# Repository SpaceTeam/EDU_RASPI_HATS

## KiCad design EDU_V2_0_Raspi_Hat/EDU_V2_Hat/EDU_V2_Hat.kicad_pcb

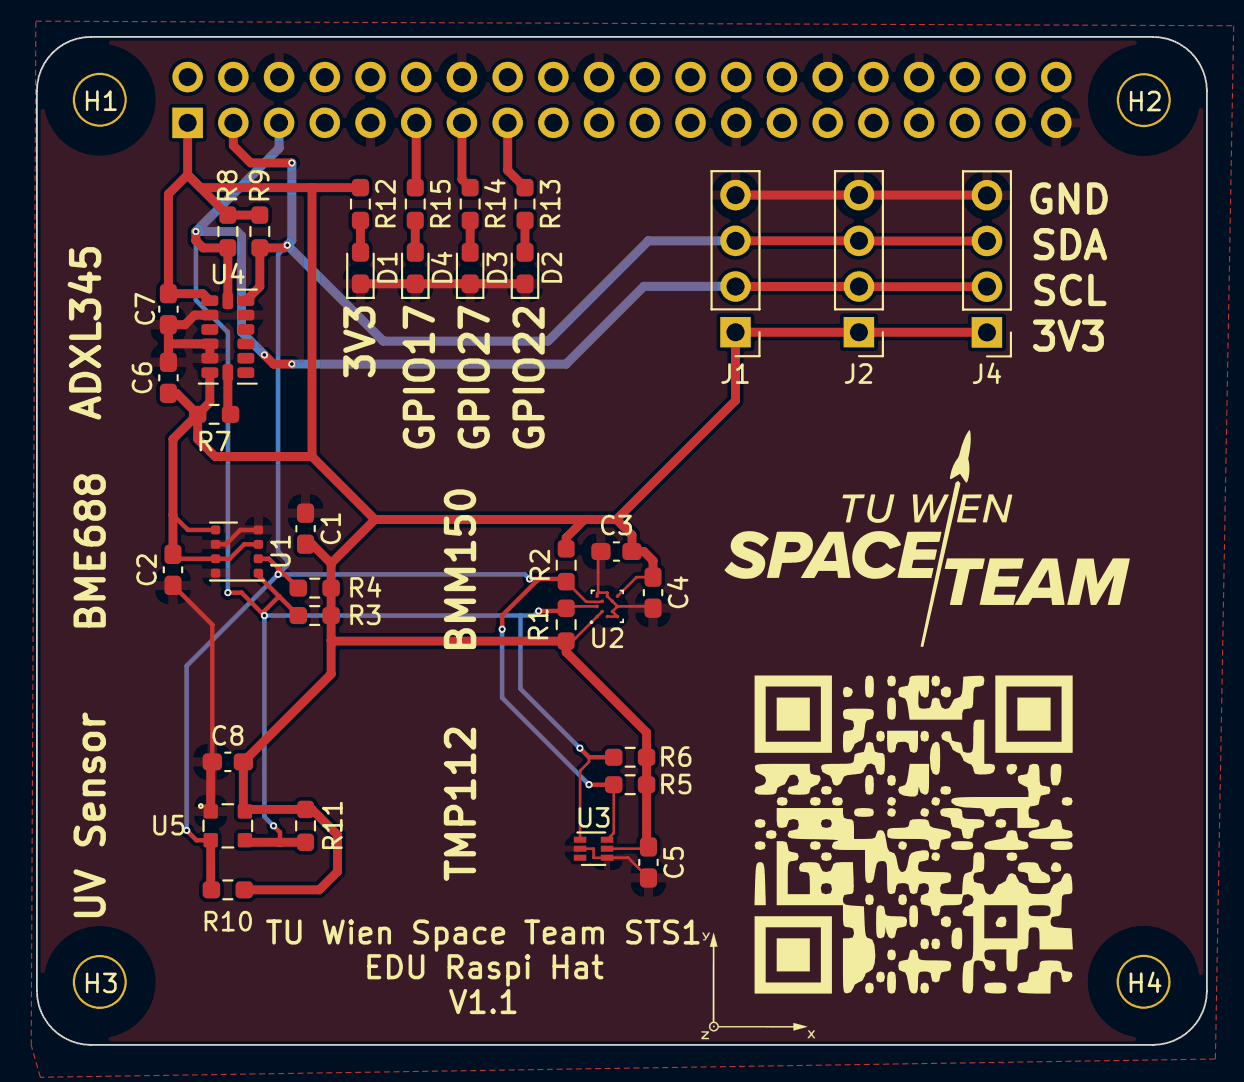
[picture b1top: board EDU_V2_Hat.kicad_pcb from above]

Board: 4 copper layers, 65.0 x 56.0 mm, 41 parts (1 on the bottom side), 12 nets.

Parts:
C1, C2, C3, C4: 100nF; C_0603_1608Metric_Pad1.08x0.95mm_HandSolder
C5: 0.01µF; C_0603_1608Metric_Pad1.08x0.95mm_HandSolder
C6: 0.1µF; C_0603_1608Metric_Pad1.08x0.95mm_HandSolder
C7: 1µF; C_0603_1608Metric_Pad1.08x0.95mm_HandSolder
C8: 1uF; C_0603_1608Metric_Pad1.08x0.95mm_HandSolder
D1, D2, D3, D4: LED; LED_0603_1608Metric_Pad1.05x0.95mm_HandSolder
H1, H2, H3, H4: 3mm_Mounting_Hole; NPTH_3mm_ID
J1, J2, J4: Conn_01x04; PinHeader_1x04_P2.54mm_Vertical
J3: 40HAT; PinSocket_2x20_P2.54mm_Vertical
R1, R2, R10, R11: 4k7; R_0603_1608Metric_Pad0.98x0.95mm_HandSolder
R3, R4, R5, R6, R7, R8, R9: 5k; R_0603_1608Metric_Pad0.98x0.95mm_HandSolder
R12, R13, R14, R15: 1k; R_0603_1608Metric_Pad0.98x0.95mm_HandSolder
U1: BME688; Bosch_LGA-8_3x3mm_P0.8mm_ClockwisePinNumbering
U1#2: coordinate_system; Coordinates
U2: BMM150; WLCSP-12_1.56x1.56mm_P0.4mm
U3: TMP112AIDRLT; SOT-563
U4: ADXL345BCCZ-RL; LGA-14_3x5mm_P0.8mm_LayoutBorder1x6y
U5: GUVA-C32SM; OLGA 2mm x 2,3mm

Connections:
3V3: C1.2, C2.2, C3.2, C4.1, C5.1, C6.1, C7.1, C8.2, J1.1, J2.1, J3.1 (P3V3), J4.1, R1.2, R2.2, R3.2, R4.2, R5.2, R6.2, R7.1, R8.1, R9.1, R10.2, R11.2, R12.1, U1.2 (CSB), U1.6 (VDDIO), U1.8 (VDD), U2.A1 (PS), U2.B2 (VDDIO), U2.E5 (VDD), U3.5 (V+), U4.1 (VDDIO), U4.6 (VS), U5.4 (VCC)
CM_SCL0: J1.2, J2.2, J3.5 (BCM3), J4.2, R1.1, R3.1, R6.1, R8.2, R11.1, U1.4 (SCK), U2.A3 (SCK), U3.1 (SCL), U4.14 (SCL/SCLK), U5.3 (SCL)
CM_SDA0: J1.3, J2.3, J3.3 (BCM2), J4.3, R2.1, R4.1, R5.1, R9.2, R10.1, U1.3 (SDI), U2.B4 (SDI), U3.6 (SDA), U4.13 (SDA/SDI/SDIO), U5.2 (SDA)
GND: C1.1, C2.1, C3.1, C4.2, C5.2, C6.2, C7.2, C8.1, D1.1 (K), D2.1 (K), D3.1 (K), D4.1 (K), J1.4, J2.4, J3.6 (GND), J3.9 (GND), J3.14 (GND), J3.20 (GND), J3.25 (GND), J3.30 (GND), J3.34 (GND), J3.39 (GND), J4.4, U1.1 (GND), U1.5 (SDO), U1.7 (GND), U2.A5 (CSB), U2.C1 (SDO), U2.C5 (GND), U2.D2 (INT), U2.D4 (DRDY), U2.E1 (GND), U2.E3 (GND), U3.2 (GND), U3.4 (ADD0), U4.2 (GND@1), U4.4 (GND@2), U4.5 (GND@3), U4.12 (SDO/ALT/ADDRESS), U5.1 (GND)
GPIO17: J3.11 (BCM17), R15.1
GPIO22: J3.15 (BCM22), R13.1
GPIO27: J3.13 (BCM27), R14.1
unnamed: D1.2 (A), R12.2
unnamed: D2.2 (A), R13.2
unnamed: D3.2 (A), R14.2
unnamed: D4.2 (A), R15.2
unnamed: R7.2, U4.7 (~CS)

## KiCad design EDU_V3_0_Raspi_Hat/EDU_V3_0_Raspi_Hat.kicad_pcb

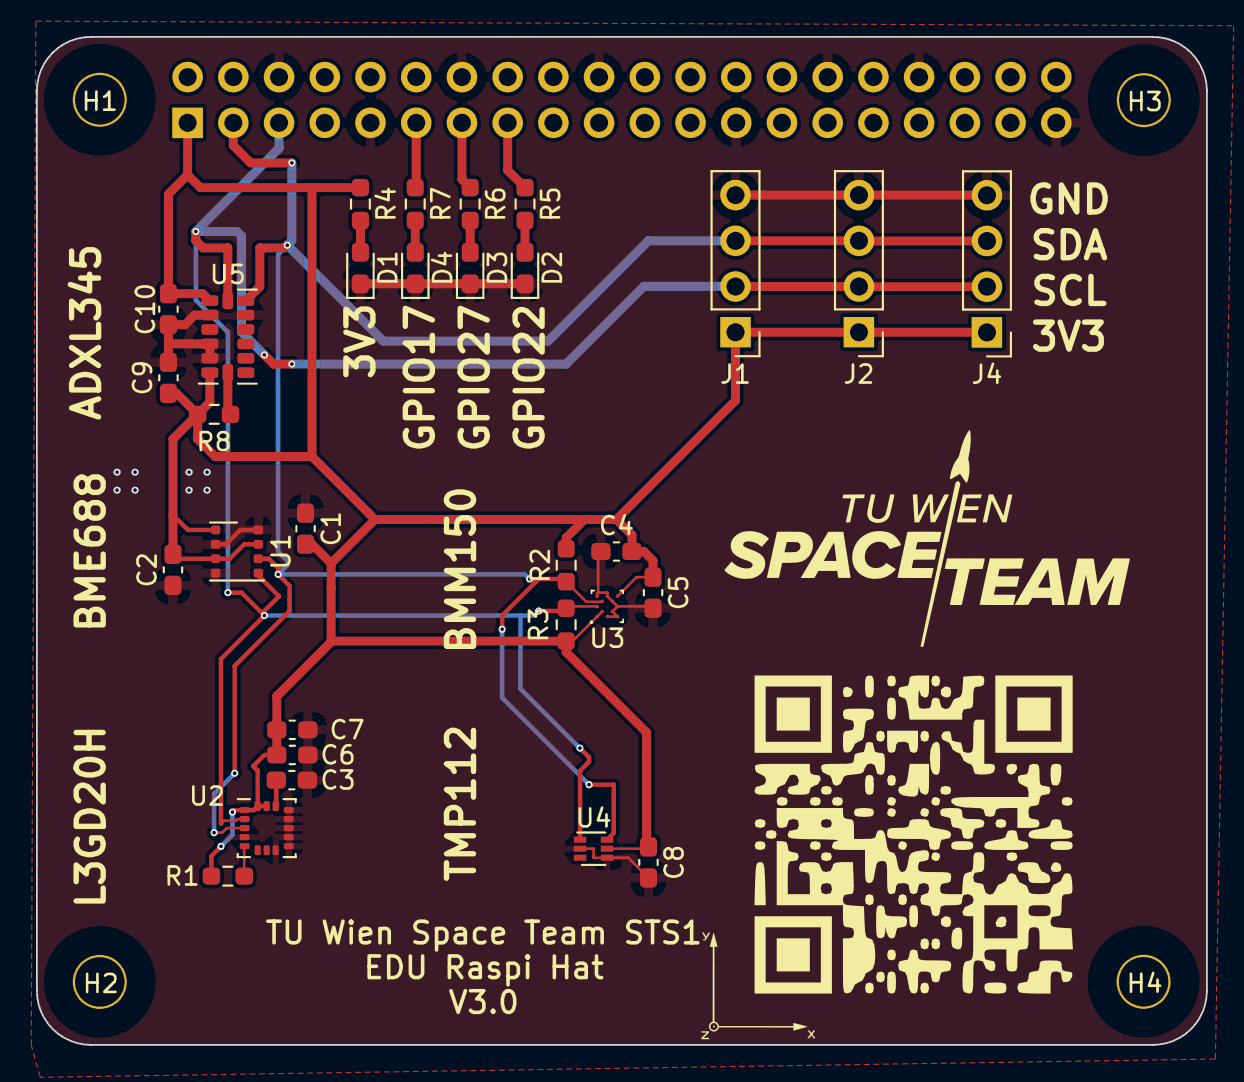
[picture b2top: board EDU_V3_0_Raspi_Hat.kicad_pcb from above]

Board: 4 copper layers, 65.0 x 56.0 mm, 36 parts (1 on the bottom side), 14 nets.

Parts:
C1, C2, C4, C5, C6, C9: 100nF; C_0603_1608Metric_Pad1.08x0.95mm_HandSolder
C3: 10nF 25V; C_0603_1608Metric_Pad1.08x0.95mm_HandSolder
C7: 10uF; C_0603_1608Metric_Pad1.08x0.95mm_HandSolder
C8: 10nF; C_0603_1608Metric_Pad1.08x0.95mm_HandSolder
C10: 1µF; C_0603_1608Metric_Pad1.08x0.95mm_HandSolder
D1, D2, D3, D4: LED; LED_0603_1608Metric_Pad1.05x0.95mm_HandSolder
H1, H2, H3, H4: 3mm_Mounting_Hole; NPTH_3mm_ID
J1, J2, J4: Conn_01x04; PinHeader_1x04_P2.54mm_Vertical
J3: 40HAT; PinSocket_2x20_P2.54mm_Vertical
R1, R2, R3, R8: 4k7; R_0603_1608Metric_Pad0.98x0.95mm_HandSolder
R4, R5, R6, R7: 1k; R_0603_1608Metric_Pad0.98x0.95mm_HandSolder
U1: BME688; Bosch_LGA-8_3x3mm_P0.8mm_ClockwisePinNumbering
U1#2: coordinate_system; Coordinates
U2: L3GD20H; LGA-16_3x3mm_P0.5mm_LayoutBorder3x5y
U3: BMM150; WLCSP-12_1.56x1.56mm_P0.4mm
U4: TMP112AIDRLT; SOT-563
U5: ADXL345BCCZ-RL; LGA-14_3x5mm_P0.8mm_LayoutBorder1x6y

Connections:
3V3: C1.2, C2.2, C4.2, C5.1, C6.1, C7.1, C8.1, C9.1, C10.1, J1.1, J2.1, J3.1 (P3V3), J4.1, R1.1, R2.2, R3.2, R4.1, R8.1, U1.2 (CSB), U1.6 (VDDIO), U1.8 (VDD), U2.1 (VDD_IO), U2.15 (RES@4), U2.16 (VDD), U3.A1 (PS), U3.B2 (VDDIO), U3.E5 (VDD), U4.5 (V+), U5.1 (VDDIO), U5.6 (VS)
CM_SCL0: J1.2, J2.2, J3.5 (BCM3), J4.2, R3.1, U1.4 (SCK), U2.2 (SCL/SPC), U3.A3 (SCK), U4.1 (SCL), U5.14 (SCL/SCLK)
CM_SDA0: J1.3, J2.3, J3.3 (BCM2), J4.3, R2.1, U1.3 (SDI), U2.3 (SDA/SDI/SDO), U3.B4 (SDI), U4.6 (SDA), U5.13 (SDA/SDI/SDIO)
GND: C1.1, C2.1, C3.1, C4.1, C5.2, C6.2, C7.2, C8.2, C9.2, C10.2, D1.1 (K), D2.1 (K), D3.1 (K), D4.1 (K), J1.4, J2.4, J3.6 (GND), J3.9 (GND), J3.14 (GND), J3.20 (GND), J3.25 (GND), J3.30 (GND), J3.34 (GND), J3.39 (GND), J4.4, U1.1 (GND), U1.5 (SDO), U1.7 (GND), U2.4 (SDO/SA0), U2.8 (DEN), U2.9 (RES@1), U2.10 (RES@2), U2.11 (RES@3), U2.12 (GND@1), U2.13 (GND@2), U3.A5 (CSB), U3.C1 (SDO), U3.C5 (GND), U3.D2 (INT), U3.D4 (DRDY), U3.E1 (GND), U3.E3 (GND), U4.2 (GND), U4.4 (ADD0), U5.2 (GND@1), U5.4 (GND@2), U5.5 (GND@3), U5.12 (SDO/ALT/ADDRESS)
GPIO17: J3.11 (BCM17), R7.1
GPIO22: J3.15 (BCM22), R5.1
GPIO27: J3.13 (BCM27), R6.1
unnamed: D1.2 (A), R4.2
unnamed: D2.2 (A), R5.2
unnamed: D3.2 (A), R6.2
unnamed: D4.2 (A), R7.2
unnamed: C3.2, U2.14 (CAP)
unnamed: R1.2, U2.5 (CS)
unnamed: R8.2, U5.7 (~CS)

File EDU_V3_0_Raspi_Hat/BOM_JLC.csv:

Comment,Designator,Footprint,LSC Part Number
10uF,C7,0603,C91150
10nF,C8,0603,C307346
1µF,C10,0603,C106858
10nF 25V,C3,0603,C302008
100nF,"C1, C2, C4, C5, C6, C9",0603,C14663
LED Green,D1,0603,C473820
LED Red,"D3, D2, D4",0603,C2286
4k7,"R1, R2, R3, R8",0603,C285218
1k,"R4, R5, R6, R7",0603,C375503
BME688,U1,Bosch_LGA-8_3x3mm_P0.8mm_ClockwisePinNumbering,C3664478
L3GD20H,U2,LGA-16_3x3mm_P0.5mm,C128360
BMM150,U3,WLCSP-12_1.56x1.56mm_P0.4mm,C171681
TMP112AIDRLT,U4,SOT-563,C28927
ADXL345BCCZ-RL,U5,LGA-14_3x5mm_P0.8mm_LayoutBorder1x6y,C9667

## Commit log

2024-04-13 EDU_HAT_V3 with assembly files
2024-04-13 EDU_HAT_V2 with assembly files
2024-04-13 Create license
